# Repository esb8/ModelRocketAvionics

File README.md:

# Model Rocketry Flight Computer and Embedded Patch Antenna – Full PCB + Assembly

An open-source avionics system developed for **model rocketry** applications by the [Metropolitain Aerospace Rocket Society at Toronto Metropolitan University](https://marstmu.com/). Originally designed for FPV drones, this project has been adapted into a **flight computer** supporting GPS, sensor fusion, data logging, and telemetry, all within a compact, custom PCB. This board also features a **custom microstrip antenna** designed by [Javezki](https://github.com/Javezki). All schematics and KiCad 9.0 PCB design files are openly available.

---

## Overview

This project delivers a robust and flexible **flight computer** for **high-power G-80 model rockets**, built on the STM32F411CEU6 microcontroller. It provides modular avionics functionality—combining flight control, telemetry, power management rated for 1S-2S LiPo, and sensor integration—making it suitable for in-flight data acquisition, staging logic, and recovery system deployment.

---

## Hardware Overview

### **Integrated Flight Computer Design**
- **Flight Computer**: RP2040 
- **Power Regulation**: High-efficiency DC-DC converters (1S LiPo)
- **Telemetry**: Long-range LoRa communication
- **Sensor Suite**: Altitude, attitude, temperature, and pressure sensing

### **Interfaces & Expansion**
- SPI-connected sensor peripherals
- USB-C programming and data offloading
- JTAG/SWD debug support
- UART/FTDI interface for external modules
- Coin cell backup power for RTC
- GPS module for position logging

---

## Flight Computer Board Features

- **MCU**: RP2040 (100MHz ARM Cortex-M4)
- **Clock Source**: 12MHz external crystal
- **IMU**: ICM-42605 (gyro + accel)
- **Barometer**: BMP280 for altitude tracking
- **GNSS**: L86-M33 GPS module (GLONASS+GPS)
- **Telemetry**: SX1276 LoRa 915MHz transceiver (NiceRF)
- **Power**: USB-C input, LDOs, and external 3.3V support

---

## Power System (Planned for Rocket Integration)

- SWD Flash for in-field reprogramming
- High-efficiency DC-DC converters
- Battery support: 1-2S LiPo or custom packs
- Regulated 3.3V rail for sensitive components
- XT60 or JST input connector options

---

## Software Compatibility

- **BetaFlight** (legacy; for IMU prototyping)
- **Custom C/C++ Firmware** (recommended for real-time rocketry logic)

---

## Bill of Materials (Key Components)

| Component         | Description                         | Specification                             |
|------------------|-------------------------------------|-------------------------------------------|
| Frame            | Enclosure/Avionics Bay              | Custom 3D-printed or machined             |
| MCU              | STM32F411CEU6                       | ARM Cortex M4 100MHz                      |
| GPS              | L86-M33                             | GNSS Positioning                          |
| IMU              | ICM-42605                           | 6DOF motion tracking                      |
| Barometer        | BMP280                              | Pressure & altitude sensor                |
| Radio            | SX1276 LoRa                         | 915MHz telemetry                          |
| Battery          | LiPo / Rocket battery pack          | 1S–2S supported via DC regulation         |
| Connectors       | USB-C, JST, XT60                    | Power + Programming                       |
| Antenna          | SMA 915MHz                          | Half-dipole LoRa                          |

---

## Tools & Assembly Requirements

- Soldering iron + fine solder
- Heat shrink tubing
- Multimeter & continuity tester
- LiPo battery charger (if applicable)
- Debug tools: ST-Link V2 / J-Link
- KiCad (PCB design and modification)
- Screws, standoffs, foam tape, zip ties

---

## Required Knowledge

- Soldering and PCB assembly
- STM32 microcontroller basics
- Familiarity with LoRa/telemetry systems
- Firmware flashing and serial debugging
- Understanding model rocketry avionics architecture

---

## Calculations

### Altimeter/Flight Timing Logic
- Barometer resolution: ±1 meter (BMP280)
- GPS fix interval: 1Hz–10Hz (L86-M33)
- IMU update: Up to 1kHz via SPI

### Power Budget
- MCU current draw: ~50mA
- LoRa TX Peak: ~120mA
- Sensors + GPS: ~30–50mA
- Total ~200–250mA @ 3.3V (0.7–1W typical)

---

## Testing & Validation

1. Flash microcontroller via SWD
2. USB-C serial communication verification
3. IMU and GPS data output test
4. Barometer altitude validation
5. LoRa telemetry range and signal integrity
6. Full ground simulation test (power cycling, resets)
7. Field tests (static fire or live launch)

---

## Media

### Flight Computer – 3D Model

### Flight Computer – PCB

### Flight Computer – Schematic

## Collaboration

This system is being developed by **Evan Bhogal** and **Javezki** for the **Metropolitan Aerospace Rocket Society at TMU** for use in high-power rocketry and avionics research.

---

## License

Released under the **MIT License**. All PCB files, schematics, and firmware modifications are open source and may be reused and modified with appropriate attribution.

---

## Resources

- [Metropolitan Aerospace Rocket Society](https://marstmu.com)
- [Javezki Github](https://github.com/Javezki)
- [ESB8 GitHub](https://github.com/esb8)
  
---

*This avionics platform bridges the gap between custom hardware and flight-ready model rocketry systems, enabling high-altitude data logging, telemetry, and robust in-flight control capabilities.*

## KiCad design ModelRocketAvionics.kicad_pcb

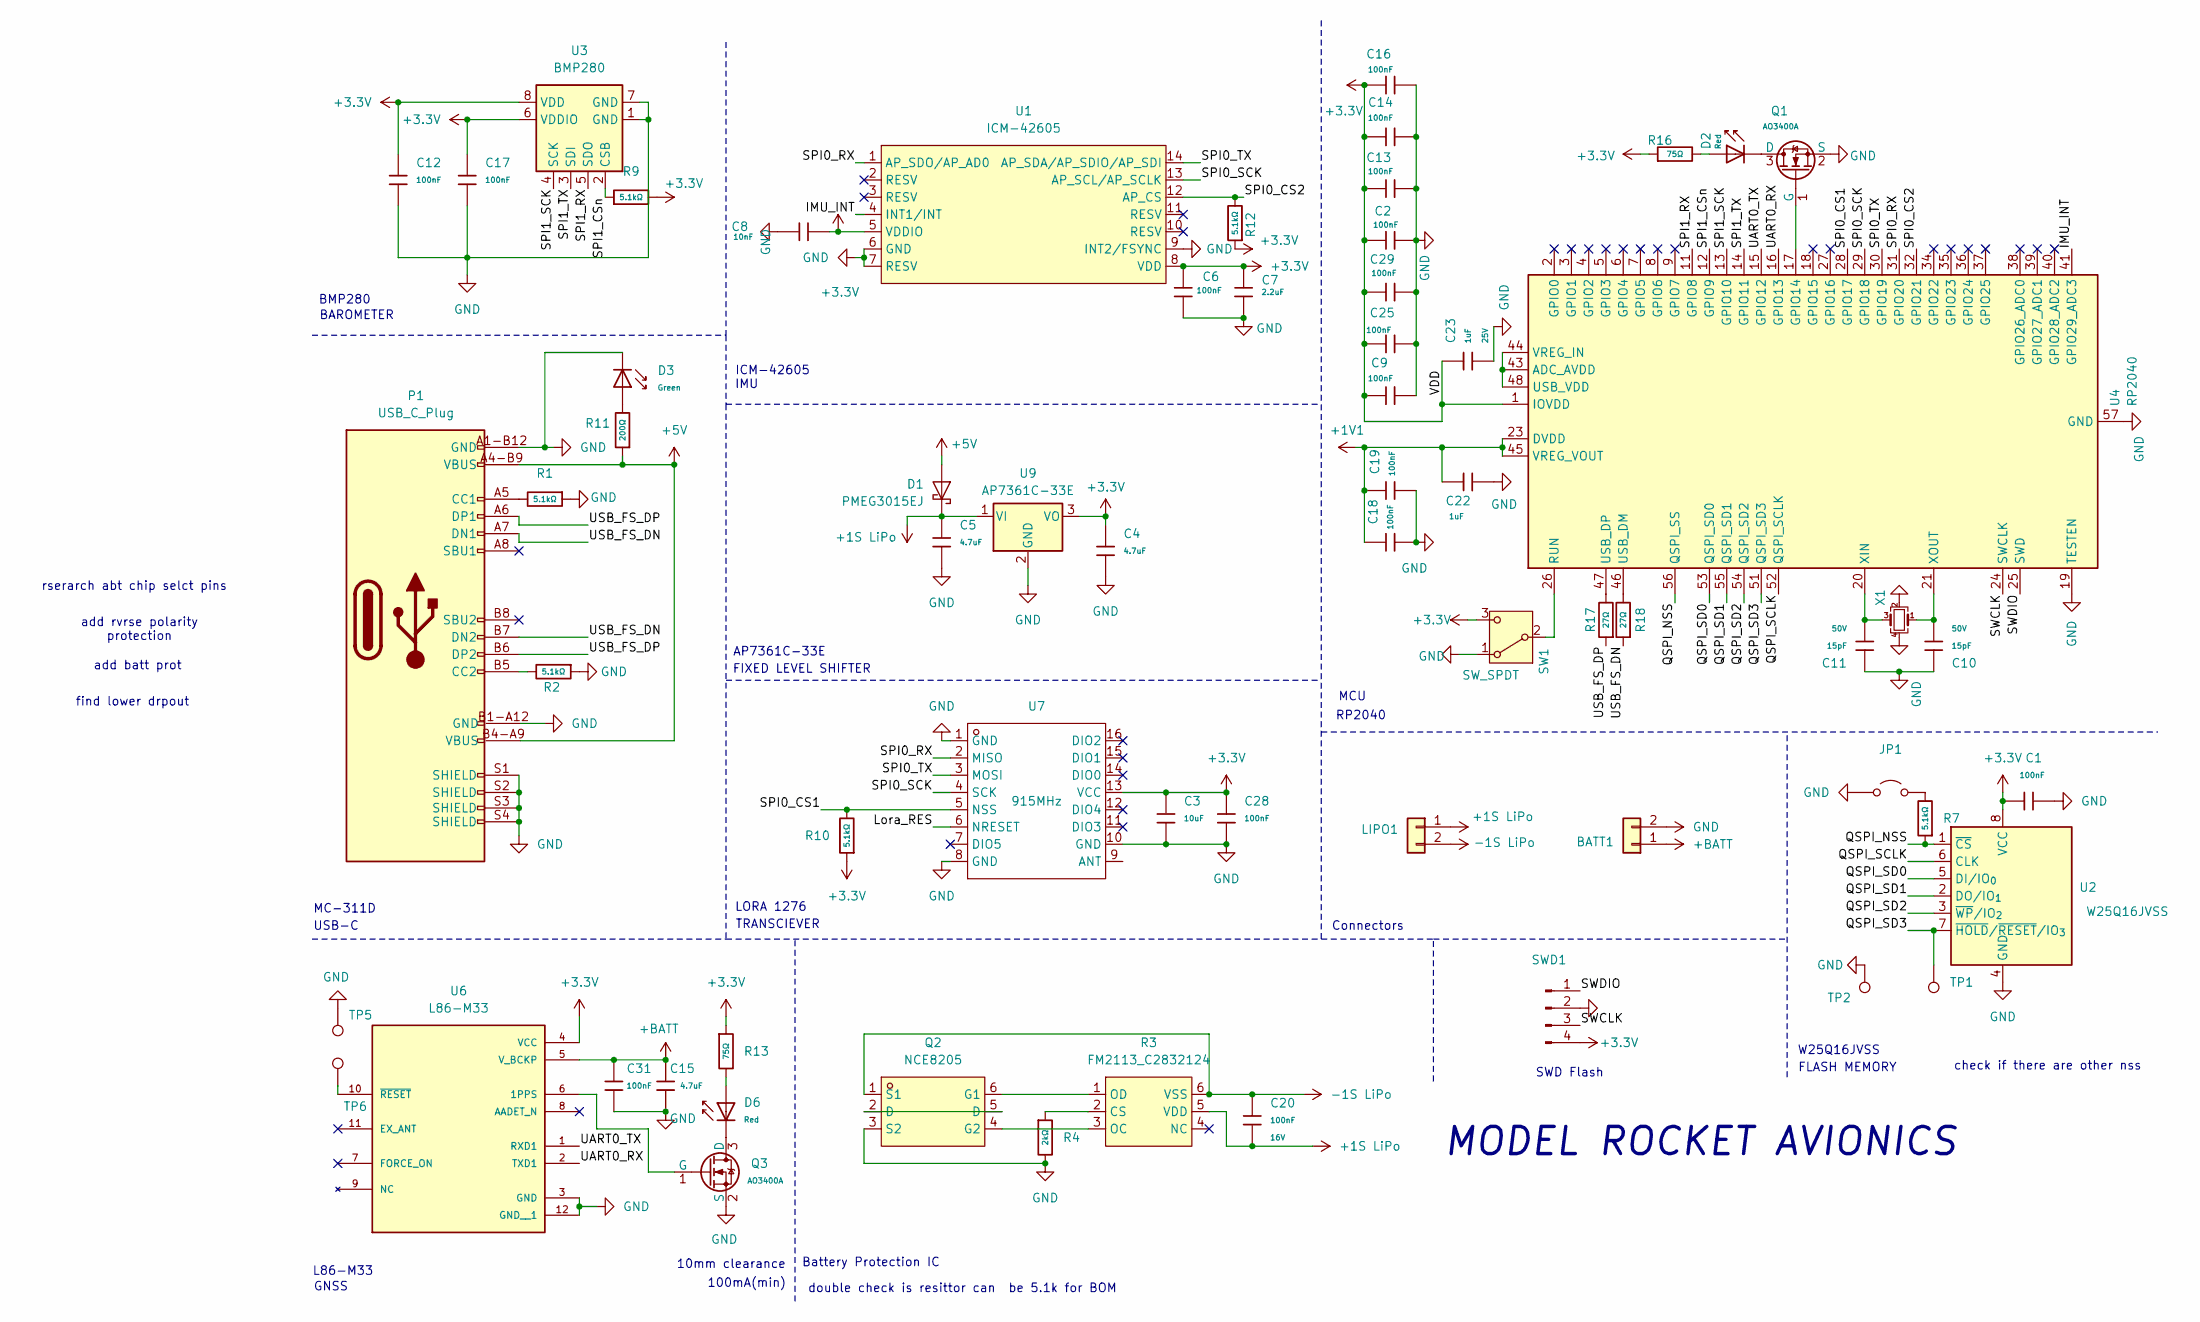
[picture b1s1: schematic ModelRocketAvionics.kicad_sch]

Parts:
BATT1: Connector; CONN-TH_B2B-XH-A-LF-SN; LCSC Part Number C158012
C1, C2, C6, C9, C12, C13, C14, C16, C17, C18, C19, C25, C28, C29, C31: 100nF; C_0402; Voltage Rated 16V; Tolerance ±10%; Part CL05B104KO5NNNC; LCSC Part Number C1525
C3: 10uF; C_0402; Voltage Rated 6.3V; Tolerance ±20%; Part CL05A106MQ5NUNC; LCSC C15525
C4, C5, C15: 4.7uF; C_0402; Voltage Rated 10V; Tolerance ±20%; Part CL05A475MP5NRNC; LCSC Part Number C23733
C7: 2.2uF; C_0402; Voltage Rated 10V; Tolerance ±10%; Part CL05A225MQ5NSNC; LCSC Part Number C2999759
C8: 10nF; C_0402; Voltage Rated 50V; Tolerance ±10%; Part CL05B103KB5NNNC; LCSC Part Number C15195
C10, C11: 15pF; C_0402; Voltage Rated 50V; Tolerance ±5%; Part 0402CG150J500NT; LCSC C1548
C20: 100nF; C_0402; Voltage Rated 16V; Tolerance ±10%; Part CL05B104KO5NNNC; LCSC C1525
C22, C23: 1uF; C_0402; Voltage Rated 25V; Tolerance ±10%; Part CL05A105KA5NQNC; LCSC C52923
D1: PMEG3015EJ; D_SOD-323F; LCSC Part Number C32798641
D2, D6: Red; D_0805; Forward Voltage (VF) 1.6V~2.6V; Part NCD0805R1; LCSC Part Number C84256
D3: Green; D_0805; Part KT-0805G; LCSC Part Number C2297
JP1: Jumper_2_Open
LIPO1: Connector; CONN-TH_B2B-XH-A-LF-SN; LCSC Part Number C158012
P1: USB_C_Plug; USB_C_Receptacle_GCT_USB4105-xx-A_16P_TopMnt_Horizontal; LCSC Part Number C136423
Q1, Q3: AO3400A; Q_SOT-23; Part AO3400A; LCSC Part Number C20917
Q2: NCE8205; SOT-23-6_L2.9-W1.6-P0.95-LS2.8-BL; LCSC Part C502858
R1, R2, R7, R9, R10, R12: 5.1kΩ; R_0402_1005Metric; Overload Voltage (Max) 50V; Tolerance ±1%; Part 0402WGF5101TCE; LCSC Part Number C25905
R3: FM2113_C2832124; SOT-23-6_L2.9-W1.6-P0.95-LS2.8-BR; LCSC Part C2832124
R4: 2kΩ; R_0402; Overload Voltage (Max) 50V; Tolerance ±1%; Part 0402WGF2001TCE; LCSC C4109
R11: 200Ω; R_0402_1005Metric; Overload Voltage (Max) 50V; Tolerance ±1%; Part 0402WGF2000TCE; LCSC Part Number C25087
R13, R16: 75Ω; R_0603_1608Metric; Overload Voltage (Max) 75V; Tolerance ±1%; Part 0603WAF750JT5E; LCSC Part Number C4275
R17, R18: 27Ω; R_0603; Overload Voltage (Max) 75V; Tolerance ±1%; Part 0603WAF270JT5E; LCSC C25190
SW1: SW_SPDT; SW-SMD_SHOUHAN_MST-22D18G23J_C2875122; LCSC Part Number C2875122
SWD1: Conn_01x04_Pin; PinHeader_2x02_P2.00mm_Vertical; LCSC Part Number C541858
TP1, TP2, TP5, TP6: TestPoint
U1: ICM-42605; LGA-14_L3.0-W2.5-P0.50-TL; LCSC Part Number C2655099
U2: W25Q16JVSS; SOIC-8_5.3x5.3mm_P1.27mm; LCSC Part Number C131025
U3: BMP280; Bosch_LGA-8_2x2.5mm_P0.65mm_ClockwisePinNumbering; LCSC Part Number C83291
U4: RP2040; QFN-56-1EP_7x7mm_P0.4mm_EP3.2x3.2mm
U6: L86-M33; XCVR_L86-M33; Digikey Part Number 2958-L86-M33CT-ND
U7: 915MHz; COMM-SMD_LORA1276-C1-915MHZ; LCSC Part Number C3001531
U9: AP7361C-33E; SOT-223-3_TabPin2; LCSC Part Number C500795
X1: Crystal_GND24_Small; Crystal_SMD_3225-4Pin_3.2x2.5mm; LCSC C20625731

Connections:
+1S LiPo: C5.1, C20.2, D1.1 (K), LIPO1.1, R3.5 (VDD), U9.1 (VI)
+1V1: C18.1, C19.1, C22.1, U4.23 (DVDD), U4.45 (VREG_VOUT), U4.50 (DVDD)
+3.3V: C1.2, C2.1, C3.1, C4.1, C6.2, C7.1, C8.2, C9.1, C12.1, C13.1, C14.1, C16.1, C17.1, C23.1, C25.1, C28.1, C29.1, R9.2, R10.1, R12.1, R13.1, R16.1, SW1.3 (C), SWD1.4, U1.5 (VDDIO), U1.8 (VDD), U2.8 (VCC), U3.6 (VDDIO), U3.8 (VDD), U4.1 (IOVDD), U4.10 (IOVDD), U4.22 (IOVDD), U4.33 (IOVDD), U4.42 (IOVDD), U4.49 (IOVDD), U6.4 (VCC), U7.13 (VCC), U9.3 (VO)
+5V: D1.2 (A), P1.A4-B9 (VBUS), P1.B4-A9 (VBUS), R11.1
+BATT: BATT1.1, C15.1, C31.1, U6.5 (V_BCKP)
-1S LiPo: C20.1, LIPO1.2, Q2.1 (S1), R3.6 (VSS)
/IMU_INT: U1.4 (INT1/INT), U4.41 (GPIO29_ADC3)
/Lora_RES: U7.6 (NRESET)
/QSPI_NSS: R7.1, U2.1 (~CS), U4.56 (QSPI_SS)
/QSPI_SCLK: U2.6 (CLK), U4.52 (QSPI_SCLK)
/QSPI_SD0: U2.5 (DI/IO_{0}), U4.53 (QSPI_SD0)
/QSPI_SD1: U2.2 (DO/IO_{1}), U4.55 (QSPI_SD1)
/QSPI_SD2: U2.3 (~WP/IO_{2}), U4.54 (QSPI_SD2)
/QSPI_SD3: TP1.1, U2.7 (~HOLD/~RESET/IO_{3}), U4.51 (QSPI_SD3)
/SPI0_CS1: R10.2, U4.28 (GPIO17), U7.5 (NSS)
/SPI0_CS2: R12.2, U1.12 (AP_CS), U4.32 (GPIO21)
/SPI0_RX: U1.1 (AP_SDO/AP_AD0), U4.31 (GPIO20), U7.2 (MISO)
/SPI0_SCK: U1.13 (AP_SCL/AP_SCLK), U4.29 (GPIO18), U7.4 (SCK)
/SPI0_TX: U1.14 (AP_SDA/AP_SDIO/AP_SDI), U4.30 (GPIO19), U7.3 (MOSI)
/SPI1_CSn: R9.1, U3.2 (CSB), U4.12 (GPIO9)
/SPI1_RX: U3.5 (SDO), U4.11 (GPIO8)
/SPI1_SCK: U3.4 (SCK), U4.13 (GPIO10)
/SPI1_TX: U3.3 (SDI), U4.14 (GPIO11)
/SWCLK: SWD1.3, U4.24 (SWCLK)
/SWDIO: SWD1.1, U4.25 (SWD)
/UART0_RX: U4.16 (GPIO13), U6.2 (TXD1)
/UART0_TX: U4.15 (GPIO12), U6.1 (RXD1)
/USB_FS_DN: P1.A7 (DN1), P1.B7 (DN2), R18.1
/USB_FS_DP: P1.A6 (DP1), P1.B6 (DP2), R17.1
GND: BATT1.2, C1.1, C2.2, C3.2, C4.2, C5.2, C6.1, C7.2, C8.1, C9.2, C10.1, C11.1, C12.2, C13.2, C14.2, C15.2, C16.2, C17.2, C18.2, C19.2, C22.2, C23.2, C25.2, C28.2, C29.2, C31.2, D3.1, JP1.1 (A), P1.A1-B12 (GND), P1.B1-A12 (GND), P1.S1 (SHIELD), P1.S2 (SHIELD), P1.S3 (SHIELD), P1.S4 (SHIELD), Q1.2 (S), Q2.3 (S2), Q3.2 (S), R1.1, R2.1, R4.2, SW1.1 (A), SWD1.2, TP2.1, TP5.1, U1.6 (GND), U1.7 (RESV), U1.9 (INT2/FSYNC), U2.4 (GND), U3.1 (GND), U3.7 (GND), U4.19 (TESTEN), U4.57 (GND), U6.3 (GND), U6.12 (GND__1), U7.1 (GND), U7.8 (GND), U7.10 (GND), U9.2 (GND), X1.2, X1.4
unnamed: D2.2, R16.2
unnamed: D3.2, R11.2
unnamed: D6.2, R13.2
unnamed: JP1.2 (B), R7.2
unnamed: P1.A5 (CC1), R1.2
unnamed: P1.B5 (CC2), R2.2
unnamed: D2.1, Q1.3 (D)
unnamed: Q1.1 (G), U4.17 (GPIO14)
unnamed: Q2.2 (D), Q2.5 (D)
unnamed: Q2.6 (G1), R3.1 (OD)
unnamed: Q2.4 (G2), R3.3 (OC)
unnamed: D6.1, Q3.3 (D)
unnamed: Q3.1 (G), U6.6 (1PPS)
unnamed: R3.2 (CS), R4.1
unnamed: SW1.2 (B), U4.26 (RUN)
unnamed: U4.43 (ADC_AVDD), U4.44 (VREG_IN), U4.48 (USB_VDD)
unnamed: R18.2, U4.46 (USB_DM)
unnamed: R17.2, U4.47 (USB_DP)
unnamed: C11.2, U4.20 (XIN), X1.3
unnamed: C10.2, U4.21 (XOUT), X1.1
unnamed: TP6.1, U6.10 (~RESET)

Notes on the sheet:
TRANSCIEVER
FLASH MEMORY
MODEL ROCKET AVIONICS
ICM-42605
L86-M33
double check is resittor can be 5.1k for BOM
IMU
add batt prot
MC-311D
SWD Flash
100mA(min)
AP7361C-33E
FIXED LEVEL SHIFTER
BAROMETER
Connectors
Battery Protection IC
USB-C
check if there are other nss
10mm clearance
BMP280
rserarch abt chip selct pins
RP2040
add rvrse polarity protection
GNSS
MCU
W25Q16JVSS
find lower drpout
LORA 1276

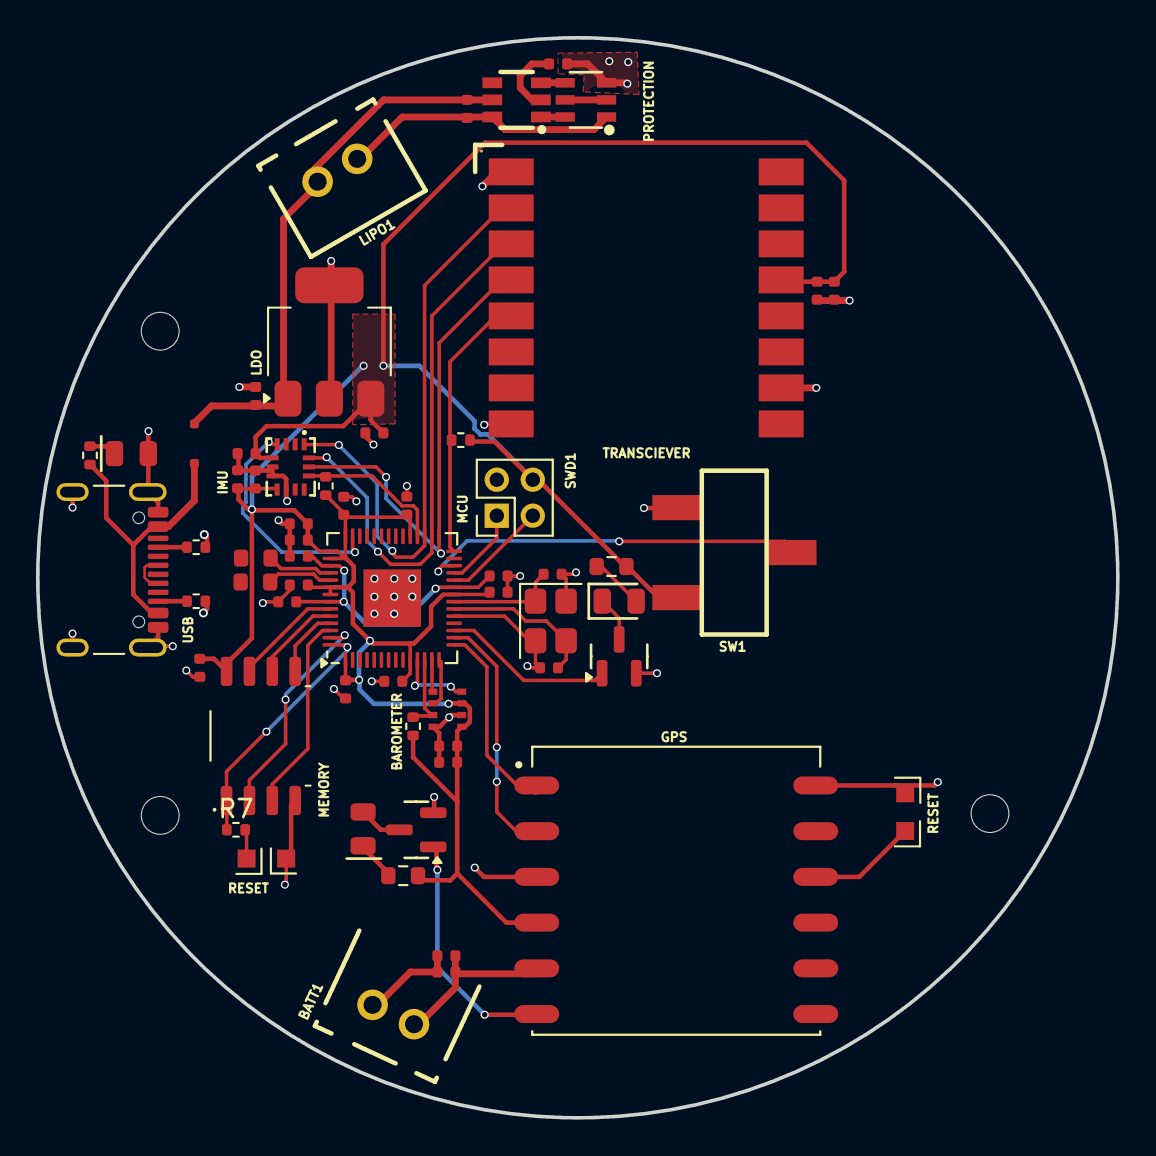
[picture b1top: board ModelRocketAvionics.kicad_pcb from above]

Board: 4 copper layers, 60.0 x 60.0 mm, 59 parts (0 on the bottom side), 48 nets.

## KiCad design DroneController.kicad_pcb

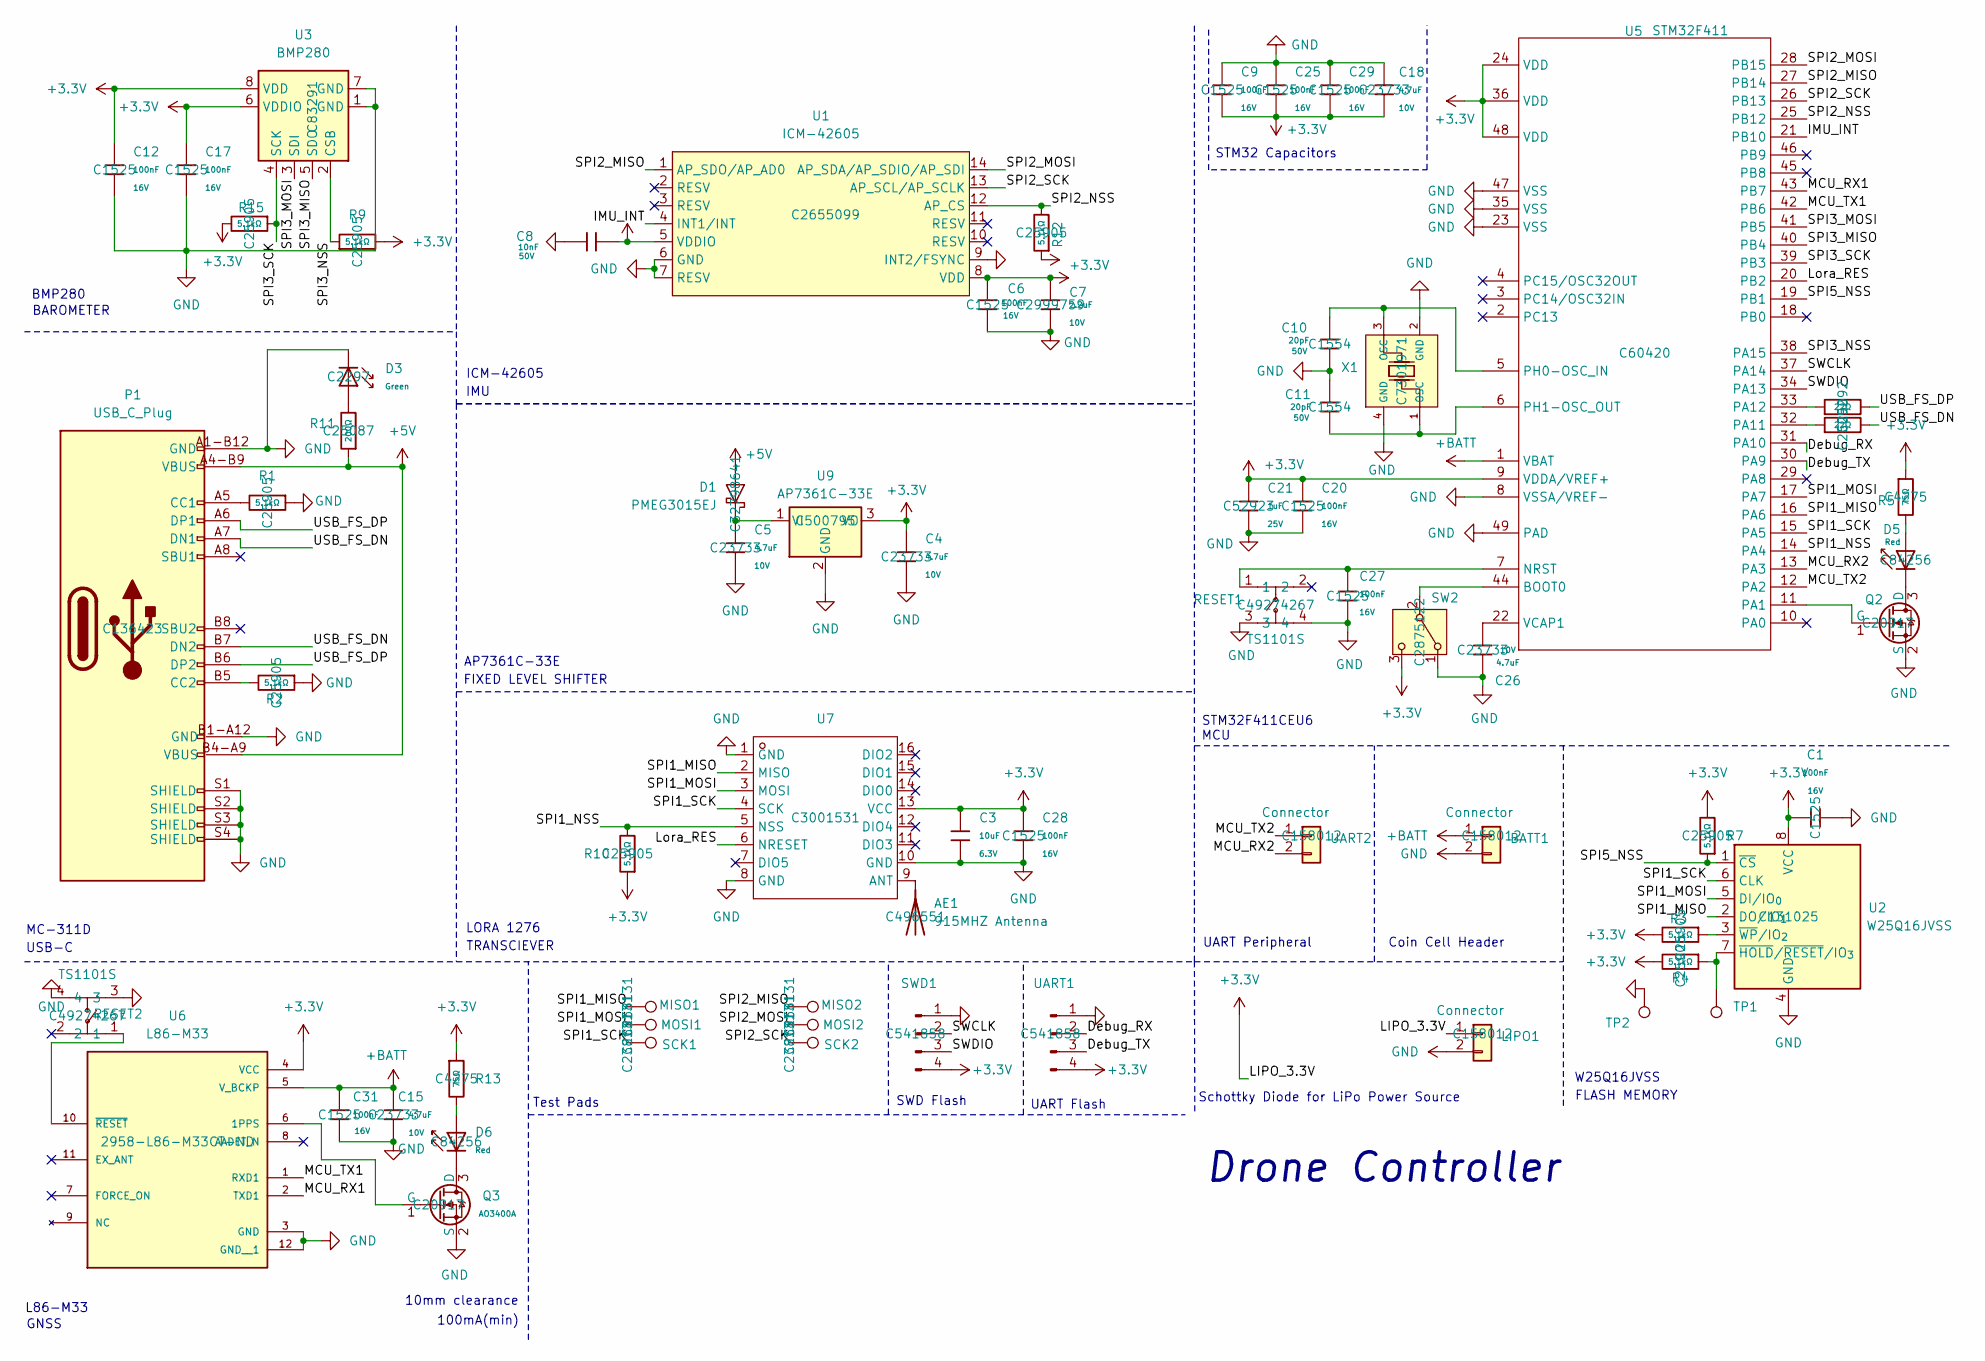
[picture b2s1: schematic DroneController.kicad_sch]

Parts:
AE1: 915MHZ Antenna; SMA_BAT_Wireless_BWSMA-KWE-Z001; LCSC Part Number C496551
BATT1: Connector; CONN-TH_B2B-XH-A-LF-SN; LCSC Part Number C158012
C1, C6, C9, C12, C17, C20, C25, C27, C28, C29, C31: 100nF; C_0402; Voltage Rated 16V; Tolerance ±10%; Part CL05B104KO5NNNC; LCSC Part Number C1525
C3: 10uF; C_0402; Voltage Rated 6.3V; Tolerance ±20%; Part CL05A106MQ5NUNC; LCSC C15525
C4, C5, C15, C18, C26: 4.7uF; C_0402; Voltage Rated 10V; Tolerance ±20%; Part CL05A475MP5NRNC; LCSC Part Number C23733
C7: 2.2uF; C_0402; Voltage Rated 10V; Tolerance ±10%; Part CL05A225MQ5NSNC; LCSC Part Number C2999759
C8: 10nF; C_0402; Voltage Rated 50V; Tolerance ±10%; Part CL05B103KB5NNNC; LCSC Part Number C15195
C10, C11: 20pF; C_0402; Voltage Rated 50V; Tolerance ±5%; Part 0402CG200J500NT; LCSC Part Number C1554
C21: 1uF; C_0402; Voltage Rated 25V; Tolerance ±10%; Part CL05A105KA5NQNC; LCSC Part Number C52923
D1: PMEG3015EJ; D_SOD-323F; LCSC Part Number C32798641
D3: Green; D_0805; Part KT-0805G; LCSC Part Number C2297
D5, D6: Red; D_0805; Forward Voltage (VF) 1.6V~2.6V; Part NCD0805R1; LCSC Part Number C84256
LIPO1: Connector; CONN-TH_B2B-XH-A-LF-SN; LCSC Part Number C158012
MISO1, MISO2: TestPoint; TestPoint_Keystone_5019_Miniature; LCSC Part Number C238131
MOSI1, MOSI2: TestPoint; TestPoint_Keystone_5019_Miniature; LCSC Part Number C238131
P1: USB_C_Plug; USB-C; LCSC Part Number C136423
Q2, Q3: AO3400A; Q_SOT-23; Part AO3400A; LCSC Part Number C20917
R1, R2, R3, R4, R7, R9, R10, R12, R15: 5.1kΩ; R_0402; Overload Voltage (Max) 50V; Tolerance ±1%; Part 0402WGF5101TCE; LCSC Part Number C25905
R5, R13: 75Ω; R_0603; Overload Voltage (Max) 75V; Tolerance ±1%; Part 0603WAF750JT5E; LCSC Part Number C4275
R6, R14: 22Ω; R_0402; Overload Voltage (Max) 50V; Tolerance ±1%; Part 0402WGF220JTCE; LCSC Part Number C25092
R11: 200Ω; R_0402; Overload Voltage (Max) 50V; Tolerance ±1%; Part 0402WGF2000TCE; LCSC Part Number C25087
RESET1, RESET2: TS1101S; SW-SMD_4P-L4.5-W4.5-P3.15-LS7.5-TL; LCSC Part Number C49274267
SCK1, SCK2: TestPoint; TestPoint_Keystone_5019_Miniature; LCSC Part Number C238131
SW2: SW_SPDT; SW-SMD_SHOUHAN_MST-22D18G23J_C2875122; LCSC Part Number C2875122
SWD1: Conn_01x04_Pin; PinHeader_1x04_P2.00mm_Vertical; LCSC Part Number C541858
TP1, TP2: TestPoint
U1: ICM-42605; LGA-14_L3.0-W2.5-P0.50-TL; LCSC Part Number C2655099
U2: W25Q16JVSS; SOIC-8_5.3x5.3mm_P1.27mm; LCSC Part Number C131025
U3: BMP280; Bosch_LGA-8_2x2.5mm_P0.65mm_ClockwisePinNumbering; LCSC Part Number C83291
U5: STM32F411; QFN-48-1EP_7x7mm_P0.5mm_EP5.6x5.6mm; LCSC Part Number C60420
U6: L86-M33; XCVR_L86-M33; Digikey Part Number 2958-L86-M33CT-ND
U7: 915MHz; COMM-SMD_LORA1276-C1-915MHZ; LCSC Part Number C3001531
U9: AP7361C-33E; SOT-223-3_TabPin2; LCSC Part Number C500795
UART1: Conn_01x04_Pin; PinHeader_1x04_P2.00mm_Vertical; LCSC Part Number C541858
UART2: Connector; CONN-TH_B2B-XH-A-LF-SN; LCSC Part Number C158012
X1: Shenzhen SCTF Elec SX2B12.000F1010F30; Crystal_SMD_2520-4Pin_2.5x2.0mm; Frequency Tolerance ±10ppm; Part X322512MSB4SI; LCSC Part Number C7301971

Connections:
+3.3V: C1.2, C3.1, C4.1, C6.2, C7.1, C8.2, C9.2, C12.1, C17.1, C18.1, C20.1, C21.1, C25.2, C28.1, C29.2, LIPO1.1, R3.2, R4.2, R5.1, R7.2, R9.2, R10.1, R12.1, R13.1, R15.2, SW2.3 (C), SWD1.4, U1.5 (VDDIO), U1.8 (VDD), U2.8 (VCC), U3.6 (VDDIO), U3.8 (VDD), U5.9 (VDDA/VREF+), U5.24 (VDD), U5.36 (VDD), U5.48 (VDD), U6.4 (VCC), U7.13 (VCC), U9.3 (VO), UART1.4; also elsewhere on the board
+5V: D1.2 (A), P1.A4-B9 (VBUS), P1.B4-A9 (VBUS), R11.1
+BATT: BATT1.1, C15.1, C31.1, U5.1 (VBAT), U6.5 (V_BCKP)
/Debug_RX: U5.31 (PA10), UART1.2
/Debug_TX: U5.30 (PA9), UART1.3
/IMU_INT: U1.4 (INT1/INT), U5.21 (PB10)
/Lora_RES: U5.20 (PB2), U7.6 (NRESET)
/MCU_RX1: U5.43 (PB7), U6.2 (TXD1)
/MCU_RX2: U5.13 (PA3), UART2.2
/MCU_TX1: U5.42 (PB6), U6.1 (RXD1)
/MCU_TX2: U5.12 (PA2), UART2.1
/SPI1_MISO: MISO1.1, U2.2 (DO/IO_{1}), U5.16 (PA6), U7.2 (MISO)
/SPI1_MOSI: MOSI1.1, U2.5 (DI/IO_{0}), U5.17 (PA7), U7.3 (MOSI)
/SPI1_NSS: R10.2, U5.14 (PA4), U7.5 (NSS)
/SPI1_SCK: SCK1.1, U2.6 (CLK), U5.15 (PA5), U7.4 (SCK)
/SPI2_MISO: MISO2.1, U1.1 (AP_SDO/AP_AD0), U5.27 (PB14)
/SPI2_MOSI: MOSI2.1, U1.14 (AP_SDA/AP_SDIO/AP_SDI), U5.28 (PB15)
/SPI2_NSS: R12.2, U1.12 (AP_CS), U5.25 (PB12)
/SPI2_SCK: SCK2.1, U1.13 (AP_SCL/AP_SCLK), U5.26 (PB13)
/SPI3_MISO: U3.5 (SDO), U5.40 (PB4)
/SPI3_MOSI: U3.3 (SDI), U5.41 (PB5)
/SPI3_NSS: R9.1, U3.2 (CSB), U5.38 (PA15)
/SPI3_SCK: R15.1, U3.4 (SCK), U5.39 (PB3)
/SPI5_NSS: R7.1, U2.1 (~CS), U5.19 (PB1)
/SWCLK: SWD1.2, U5.37 (PA14)
/SWDIO: SWD1.3, U5.34 (PA13)
/USB_FS_DN: P1.A7 (DN1), P1.B7 (DN2), R6.2
/USB_FS_DP: P1.A6 (DP1), P1.B6 (DP2), R14.2
GND: BATT1.2, C1.1, C3.2, C4.2, C5.2, C6.1, C7.2, C8.1, C9.1, C10.2, C11.1, C12.2, C15.2, C17.2, C18.2, C20.2, C21.2, C25.1, C26.2, C27.2, C28.2, C29.1, C31.2, D3.1, LIPO1.2, P1.A1-B12 (GND), P1.B1-A12 (GND), P1.S1 (SHIELD), P1.S2 (SHIELD), P1.S3 (SHIELD), P1.S4 (SHIELD), Q2.2 (S), Q3.2 (S), R1.1, R2.1, RESET1.3, RESET1.4, RESET2.3, RESET2.4, SW2.1 (A), SWD1.1, TP2.1, U1.6 (GND), U1.7 (RESV), U1.9 (INT2/FSYNC), U2.4 (GND), U3.1 (GND), U3.7 (GND), U5.8 (VSSA/VREF-), U5.23 (VSS), U5.35 (VSS), U5.47 (VSS), U5.49 (PAD), U6.3 (GND), U6.12 (GND__1), U7.1 (GND), U7.8 (GND), U7.10 (GND), U9.2 (GND), UART1.1, X1.2 (GND), X1.4 (GND); also elsewhere on the board
unnamed: AE1.1 (A), U7.9 (ANT)
unnamed: C5.1, D1.1 (K), U9.1 (VI)
unnamed: D3.2, R11.2
unnamed: D5.2, R5.2
unnamed: D6.2, R13.2
unnamed: P1.A5 (CC1), R1.2
unnamed: P1.B5 (CC2), R2.2
unnamed: D5.1, Q2.3 (D)
unnamed: Q2.1 (G), U5.11 (PA1)
unnamed: D6.1, Q3.3 (D)
unnamed: Q3.1 (G), U6.6 (1PPS)
unnamed 40: SW2.2 (B), U5.44 (BOOT0); also elsewhere on the board
unnamed: R4.1, TP1.1, U2.7 (~HOLD/~RESET/IO_{3})
unnamed: R3.1, U2.3 (~WP/IO_{2})
unnamed: C27.1, RESET1.1, U5.7 (NRST)
unnamed: R6.1, U5.32 (PA11)
unnamed: R14.1, U5.33 (PA12)
unnamed: C10.1, U5.5 (PH0-OSC_IN), X1.3 (OSC)
unnamed: C11.2, U5.6 (PH1-OSC_OUT), X1.1 (OSC)
unnamed: C26.1, U5.22 (VCAP1)
unnamed: RESET2.1, U6.10 (~RESET)

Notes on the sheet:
TRANSCIEVER
FLASH MEMORY
STM32F411CEU6
Drone Controller
ICM-42605
UART Peripheral
Coin Cell Header
L86-M33
Schottky Diode for LiPo Power Source
Test Pads
IMU
MC-311D
SWD Flash
UART Flash
100mA(min)
AP7361C-33E
FIXED LEVEL SHIFTER
BAROMETER
USB-C
10mm clearance
BMP280
STM32 Capacitors
GNSS
MCU
W25Q16JVSS
LORA 1276

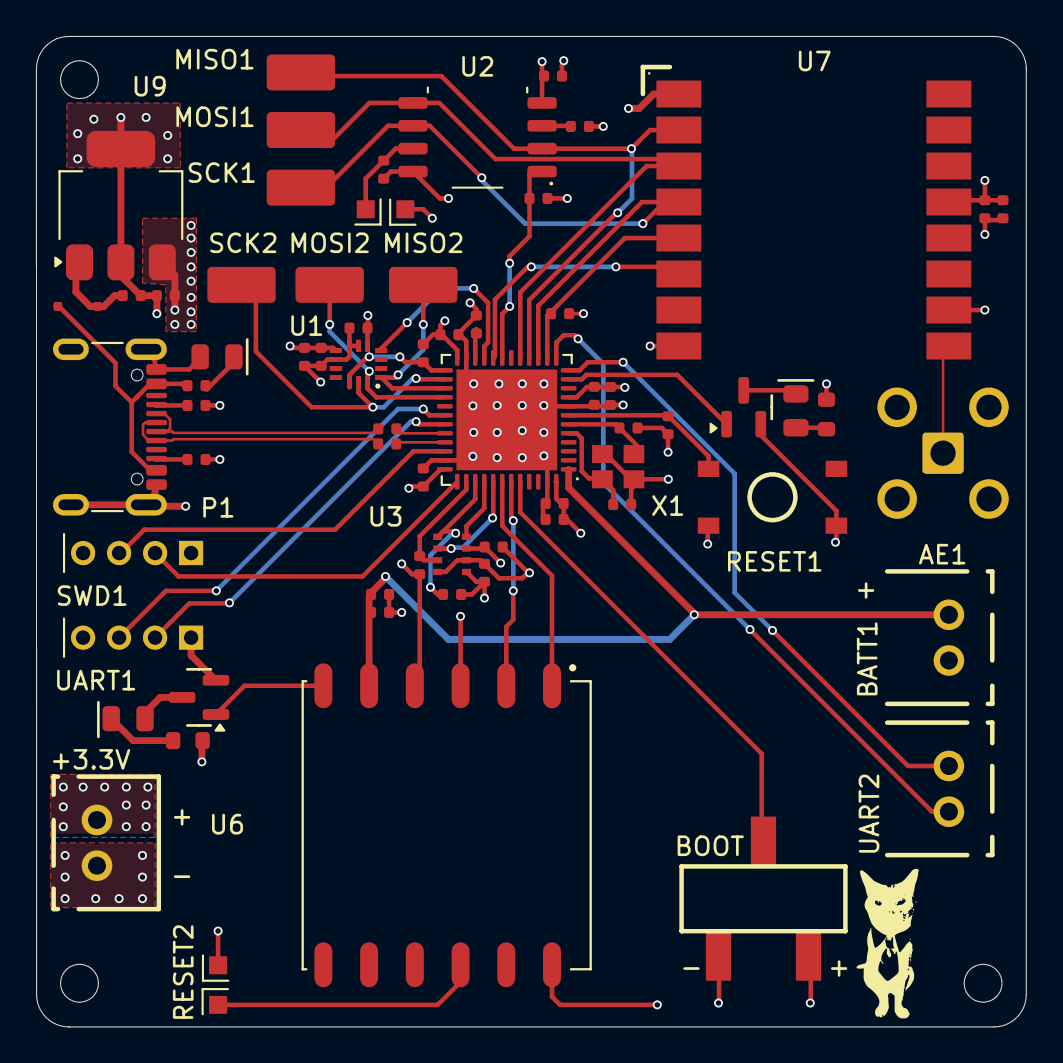
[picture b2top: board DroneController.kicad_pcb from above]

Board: 4 copper layers, 55.0 x 55.0 mm, 65 parts (0 on the bottom side), 49 nets.

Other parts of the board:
+3.3V: Connector; CONN-TH_B2B-XH-A-LF-SN
BOOT: SW_SPDT; SW-SMD_SHOUHAN_MST-22D18G23J_C2875122

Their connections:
+3.3V: +3.3V.2, BOOT.3 (C); also elsewhere on the board
GND: +3.3V.1, BOOT.1 (A); also elsewhere on the board
unnamed 40: BOOT.2 (B); also elsewhere on the board

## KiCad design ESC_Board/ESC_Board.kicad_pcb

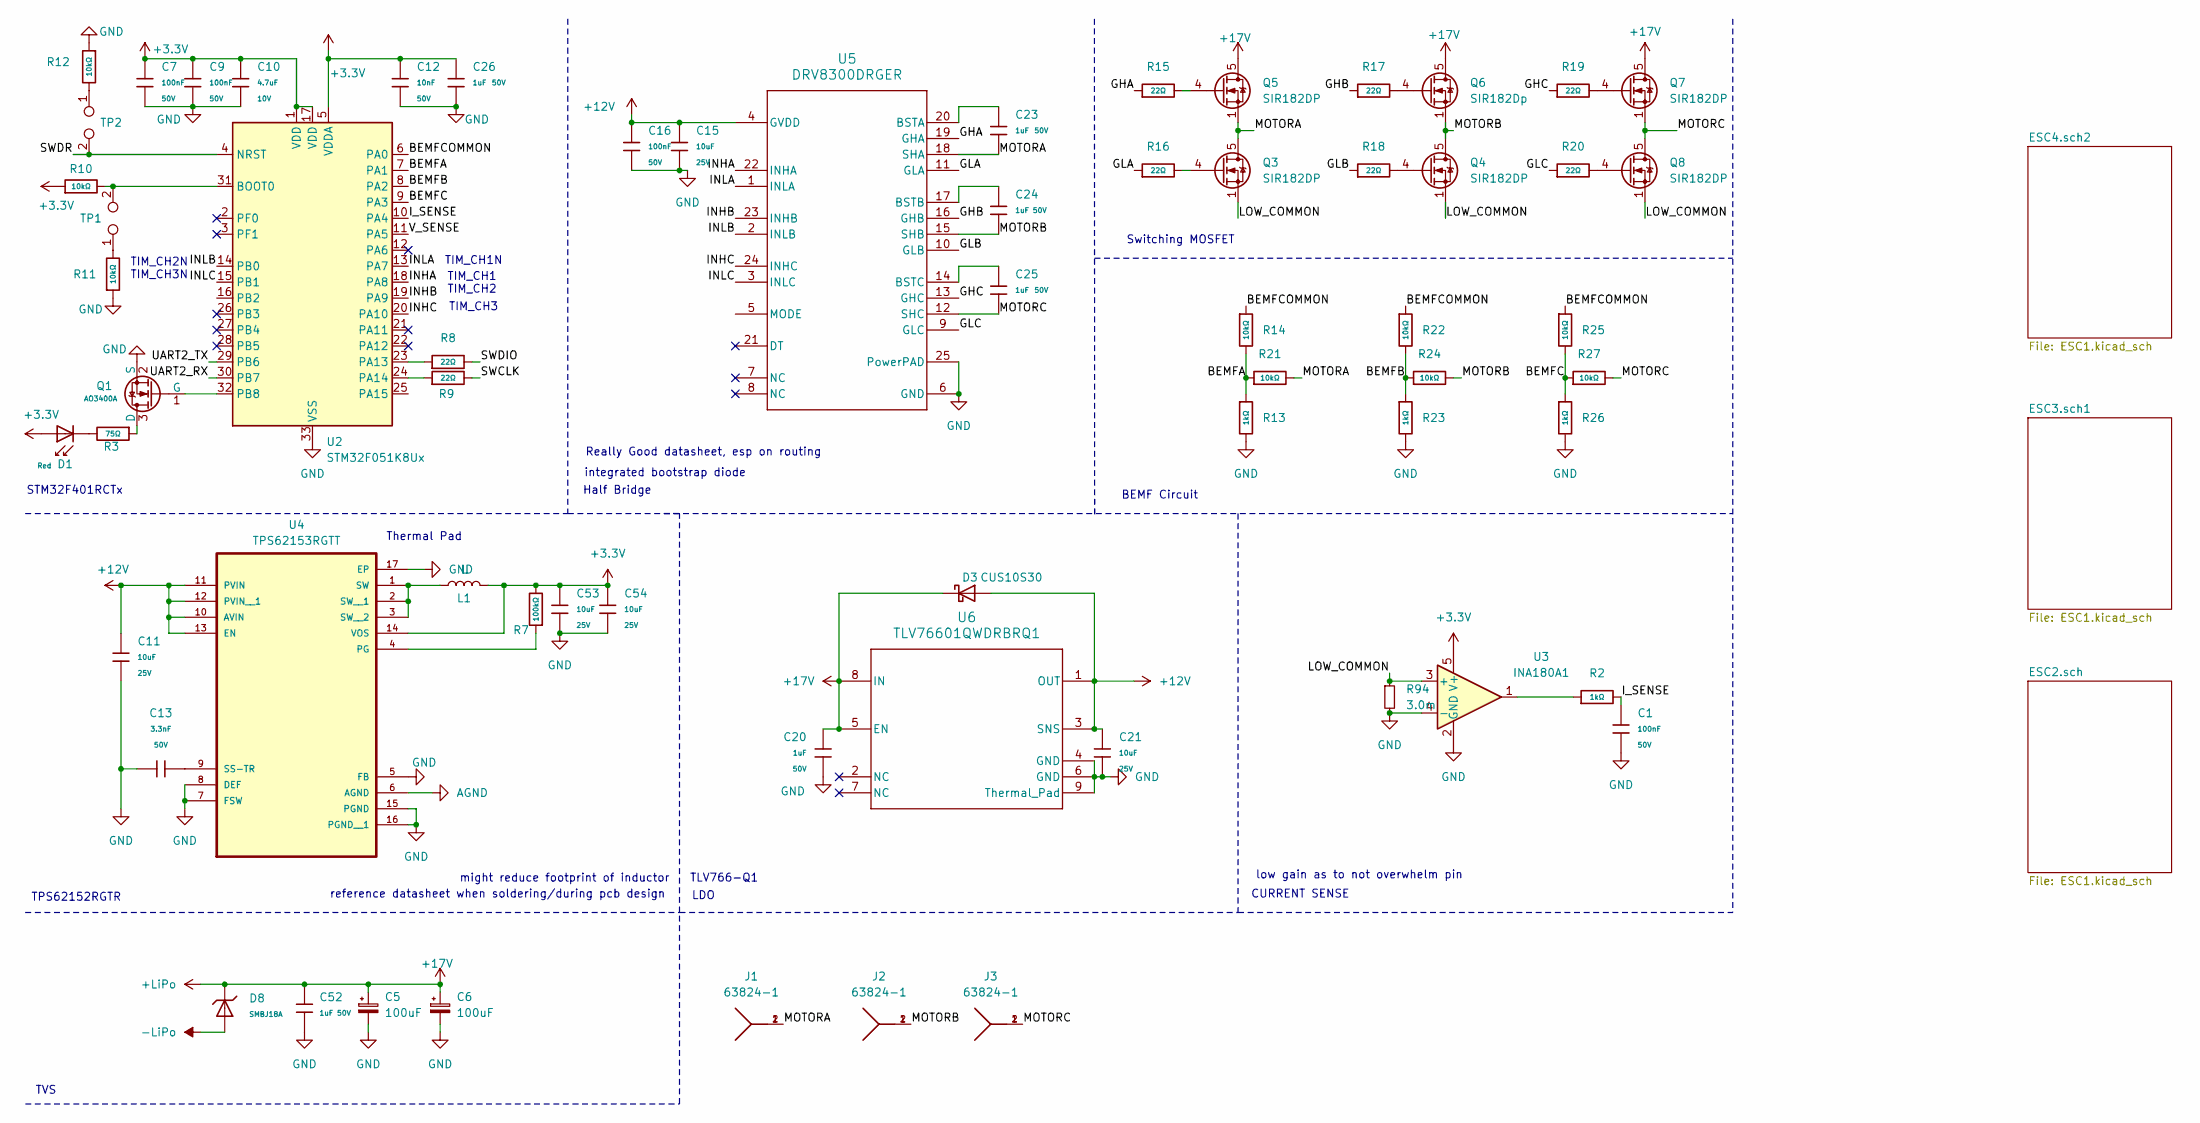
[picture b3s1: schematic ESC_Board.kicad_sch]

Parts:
C1, C7, C9, C16: 100nF; C_0402; Voltage Rated 50V; Tolerance ±10%; Part CL05B104KB54PNC; LCSC C307331
C5, C6: 100uF; CP_Elec_8x10; LCSC C445063
C10: 4.7uF; C_0402; Voltage Rated 10V; Tolerance ±20%; Part CL05A475MP5NRNC; LCSC C23733
C11, C15, C21, C53, C54: 10uF; C_0603; Voltage Rated 25V; Tolerance ±20%; Part CL10A106MA8NRNC; LCSC C96446
C12: 10nF; C_0402; Voltage Rated 50V; Tolerance ±10%; Part CL05B103KB5NNNC; LCSC C15195
C13: 3.3nF; C_0402; Voltage Rated 50V; Tolerance ±10%; Part CL05B332KB5NNNC; LCSC C26404
C20, C23, C24, C25, C26, C52: 1uF; C_0603; Voltage Rated 50V; Tolerance ±10%; LCSC C6119857
D1: Red; D_0805; Forward Voltage (VF) 1.6V~2.6V; Part NCD0805R1; LCSC C84256
D3: CUS10S30; LCSC C146335
D8: SMBJ18A; D_SMB; Part SMBJ18A; LCSC C3035859
J1, J2, J3: 63824-1; TRM2_63824-1_TEC; PART_DESCRIPTION Connector,5.08mm,Straight
L1: L; L_1008_2520Metric; LCSC C86092
Q1: AO3400A; Q_SOT-23; Part AO3400A; LCSC C20917
Q3, Q4, Q5, Q7, Q8: SIR182DP; TDSON-8-1; LCSC C151507
Q6: SIR182Dp; TDSON-8-1; LCSC C151507
R2, R13, R23, R26: 1kΩ; R_0402; Tolerance ±1%; Part HP02WAJ0102TCE; LCSC C2759467
R3: 75Ω; R_0402; Tolerance ±1%; Part 0402WGF750JTCE; LCSC C4275
R7: 100kΩ; R_0402; Tolerance ±1%; Part 0402WGF1003TCE; LCSC C25741
R8, R9, R15, R16, R17, R18, R19, R20: 22Ω; R_0402; Tolerance ±1%; LCSC C400511
R10, R11, R12, R14, R21, R22, R24, R25, R27: 10kΩ; R_0402; Tolerance ±1%; LCSC C191123
R94: 3.0m; R_2512_6332Metric; LCSC C2994640
TP1, TP2: TestPoint_2Pole
U2: STM32F051K8Ux; QFN-32-1EP_5x5mm_P0.5mm_EP3.45x3.45mm
U3: INA180A1; SOT-23-5
U4: TPS62153RGTT; TQFN-16-1EP_3x3mm_P0.5mm_EP1.6x1.6mm; LCSC C140300
U5: DRV8300DRGER; RGE0024B-IPC_A
U6: TLV76601QWDRBRQ1; DRB0008J-IPC_A

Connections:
+3.3V: C7.1, C9.1, C10.1, C12.1, C26.1, C53.2, C54.2, D1.2, L1.2, R7.2, R10.1, U2.1 (VDD), U2.5 (VDDA), U2.17 (VDD), U3.5 (V+), U4.14 (VOS); also elsewhere on the board
+12V: C11.1, C15.2, C16.1, C21.1, D3.2 (A), U4.10 (AVIN), U4.11 (PVIN), U4.12 (PVIN__1), U4.13 (EN), U5.4 (GVDD), U6.1 (OUT), U6.3 (SNS); also elsewhere on the board
+17V: C5.1, C6.1, C20.1, C52.1, D3.1 (K), D8.1, Q5.5 (D), Q6.5 (D), Q7.5 (D), U6.5 (EN), U6.8 (IN); also elsewhere on the board
-LiPo: D8.2
/BEMFA: R13.1, R14.2, R21.1, U2.7 (PA1)
/BEMFB: R22.2, R23.1, R24.1, U2.8 (PA2)
/BEMFC: R25.2, R26.1, R27.1, U2.9 (PA3)
/BEMFCOMMON: R14.1, R22.1, R25.1, U2.6 (PA0)
/GHA: R15.1, U5.19 (GHA)
/GHB: R17.1, U5.16 (GHB)
/GHC: R19.1, U5.13 (GHC)
/GLA: R16.1, U5.11 (GLA)
/GLB: R18.1, U5.10 (GLB)
/GLC: R20.1, U5.9 (GLC)
/INHA: U2.18 (PA8), U5.22 (INHA)
/INHB: U2.19 (PA9), U5.23 (INHB)
/INHC: U2.20 (PA10), U5.24 (INHC)
/INLA: U2.13 (PA7), U5.1 (INLA)
/INLB: U2.14 (PB0), U5.2 (INLB)
/INLC: U2.15 (PB1), U5.3 (INLC)
/I_SENSE: C1.1, R2.2, U2.10 (PA4)
/LOW_COMMON: Q3.1 (S), Q3.2 (S), Q3.3 (S), Q4.1 (S), Q4.2 (S), Q4.3 (S), Q8.1 (S), Q8.2 (S), Q8.3 (S), R94.1, U3.3 (+); also elsewhere on the board
/MOTORA: C23.2, J1.1, J1.2, Q3.5 (D), Q5.1 (S), Q5.2 (S), Q5.3 (S), R21.2, U5.18 (SHA); also elsewhere on the board
/MOTORB: C24.2, J2.1, J2.2, Q4.5 (D), Q6.1 (S), Q6.2 (S), Q6.3 (S), R24.2, U5.15 (SHB)
/MOTORC: C25.2, J3.1, J3.2, Q7.1 (S), Q7.2 (S), Q7.3 (S), Q8.5 (D), R27.2, U5.12 (SHC)
/SWCLK: R9.2
/SWDIO: R8.2
/SWDR: TP2.2, U2.4 (NRST)
/UART2_RX: U2.30 (PB7)
/UART2_TX: U2.29 (PB6)
/V_SENSE: U2.11 (PA5)
AGND: U4.6 (AGND)
GND: C1.2, C5.2, C6.2, C7.2, C9.2, C10.2, C11.2, C12.2, C13.1, C15.1, C16.2, C20.2, C21.2, C26.2, C52.2, C53.1, C54.1, Q1.2 (S), R11.1, R12.1, R13.2, R23.2, R26.2, R94.2, U2.33 (VSS), U3.2 (GND), U3.4 (-), U4.5 (FB), U4.7 (FSW), U4.8 (DEF), U4.15 (PGND), U4.16 (PGND__1), U4.17 (EP), U5.6 (GND), U5.25 (PowerPAD), U6.4 (GND), U6.6 (GND), U6.9 (Thermal_Pad); also elsewhere on the board
unnamed: D1.1, R3.2
unnamed: Q1.3 (D), R3.1
unnamed: Q1.1 (G), U2.32 (PB8)
unnamed 119: Q3.4 (G), R16.2; also elsewhere on the board
unnamed: Q4.4 (G), R18.2
unnamed 121: Q5.4 (G), R15.2; also elsewhere on the board
unnamed: Q6.4 (G), R17.2
unnamed: Q7.4 (G), R19.2
unnamed: Q8.4 (G), R20.2
unnamed: R2.1, U3.1
unnamed: R11.2, TP1.1
unnamed: R12.2, TP2.1
unnamed: R10.2, TP1.2, U2.31 (BOOT0)
unnamed: R8.1, U2.23 (PA13)
unnamed: R9.1, U2.24 (PA14)
unnamed: R7.1, U4.4 (PG)
unnamed: C13.2, U4.9 (SS-TR)
unnamed: L1.1, U4.1 (SW), U4.2 (SW__1), U4.3 (SW__2)
unnamed: C23.1, U5.20 (BSTA)
unnamed: C24.1, U5.17 (BSTB)
unnamed: C25.1, U5.14 (BSTC)

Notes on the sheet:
Half Bridge
TIM_CH3
integrated bootstrap diode
TIM_CH1N
STM32F401RCTx
CURRENT SENSE
BEMF Circuit
Switching MOSFET
TVS
TIM_CH2N
Really Good datasheet, esp on routing
TIM_CH3N
might reduce footprint of inductor
LDO
TLV766-Q1
reference datasheet when soldering/during pcb design
low gain as to not overwhelm pin
Thermal Pad
TIM_CH2
TIM_CH1
TPS62152RGTR
